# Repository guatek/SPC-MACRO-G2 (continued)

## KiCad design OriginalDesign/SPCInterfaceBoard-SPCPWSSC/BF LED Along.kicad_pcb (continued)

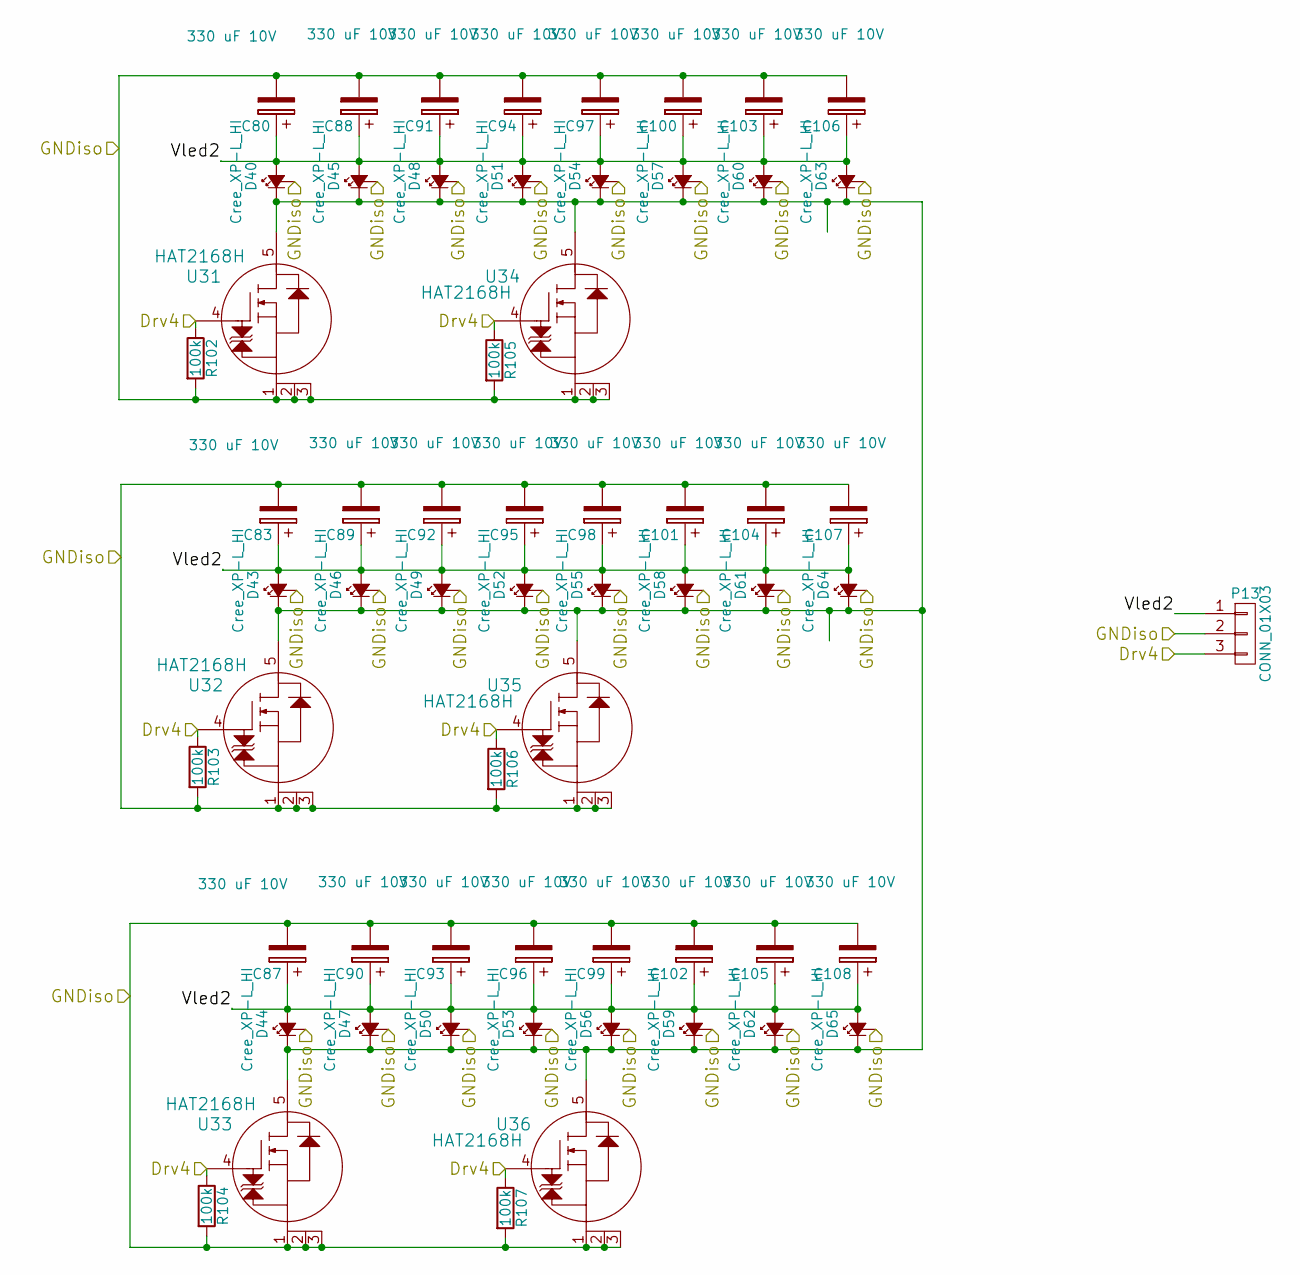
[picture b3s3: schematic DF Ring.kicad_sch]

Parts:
C80, C83, C87, C88, C89, C90, C91, C92, C93, C94, C95, C96, C97, C98, C99, C100, C101, C102, C103, C104, C105, C106, C107, C108: 330 uF 10V; TantalC_SizeD_EIA-7343_Reflow
D40, D43, D44, D45, D46, D47, D48, D49, D50, D51, D52, D53, D54, D55, D56, D57, D58, D59, D60, D61, D62, D63, D64, D65: Cree_XP-L_HI; Cree_XP-L_HI-vias-4
P13: CONN_01X03; mpt_0,5%2f3-2,54
R102, R103, R104, R105, R106, R107: 100k; r_0603
U31, U32, U33, U34, U35, U36: HAT2168H; SOT-669_LFPAK-vias

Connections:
/LED-DC-DC/Df Ring/Drv4: P13.3, R102.1, R103.1, R104.1, R105.1, R106.1, R107.1, U31.4, U32.4, U33.4, U34.4, U35.4, U36.4
/LED-DC-DC/Df Ring/GNDiso: C80.2, C83.2, C87.2, C88.2, C89.2, C90.2, C91.2, C92.2, C93.2, C94.2, C95.2, C96.2, C97.2, C98.2, C99.2, C100.2, C101.2, C102.2, C103.2, C104.2, C105.2, C106.2, C107.2, C108.2, D40.3 (PAD), D43.3 (PAD), D44.3 (PAD), D45.3 (PAD), D46.3 (PAD), D47.3 (PAD), D48.3 (PAD), D49.3 (PAD), D50.3 (PAD), D51.3 (PAD), D52.3 (PAD), D53.3 (PAD), D54.3 (PAD), D55.3 (PAD), D56.3 (PAD), D57.3 (PAD), D58.3 (PAD), D59.3 (PAD), D60.3 (PAD), D61.3 (PAD), D62.3 (PAD), D63.3 (PAD), D64.3 (PAD), D65.3 (PAD), P13.2, R102.2, R103.2, R104.2, R105.2, R106.2, R107.2, U31.1, U31.2, U31.3, U32.1, U32.2, U32.3, U33.1, U33.2, U33.3, U34.1, U34.2, U34.3, U35.1, U35.2, U35.3, U36.1, U36.2, U36.3
/LED-DC-DC/Df Ring/Vled2: C80.1, C83.1, C87.1, C88.1, C89.1, C90.1, C91.1, C92.1, C93.1, C94.1, C95.1, C96.1, C97.1, C98.1, C99.1, C100.1, C101.1, C102.1, C103.1, C104.1, C105.1, C106.1, C107.1, C108.1, D40.2 (A), D43.2 (A), D44.2 (A), D45.2 (A), D46.2 (A), D47.2 (A), D48.2 (A), D49.2 (A), D50.2 (A), D51.2 (A), D52.2 (A), D53.2 (A), D54.2 (A), D55.2 (A), D56.2 (A), D57.2 (A), D58.2 (A), D59.2 (A), D60.2 (A), D61.2 (A), D62.2 (A), D63.2 (A), D64.2 (A), D65.2 (A), P13.1
unnamed: D40.1 (K), D43.1 (K), D44.1 (K), D45.1 (K), D46.1 (K), D47.1 (K), D48.1 (K), D49.1 (K), D50.1 (K), D51.1 (K), D52.1 (K), D53.1 (K), D54.1 (K), D55.1 (K), D56.1 (K), D57.1 (K), D58.1 (K), D59.1 (K), D60.1 (K), D61.1 (K), D62.1 (K), D63.1 (K), D64.1 (K), D65.1 (K), U31.5, U32.5, U33.5, U34.5, U35.5, U36.5

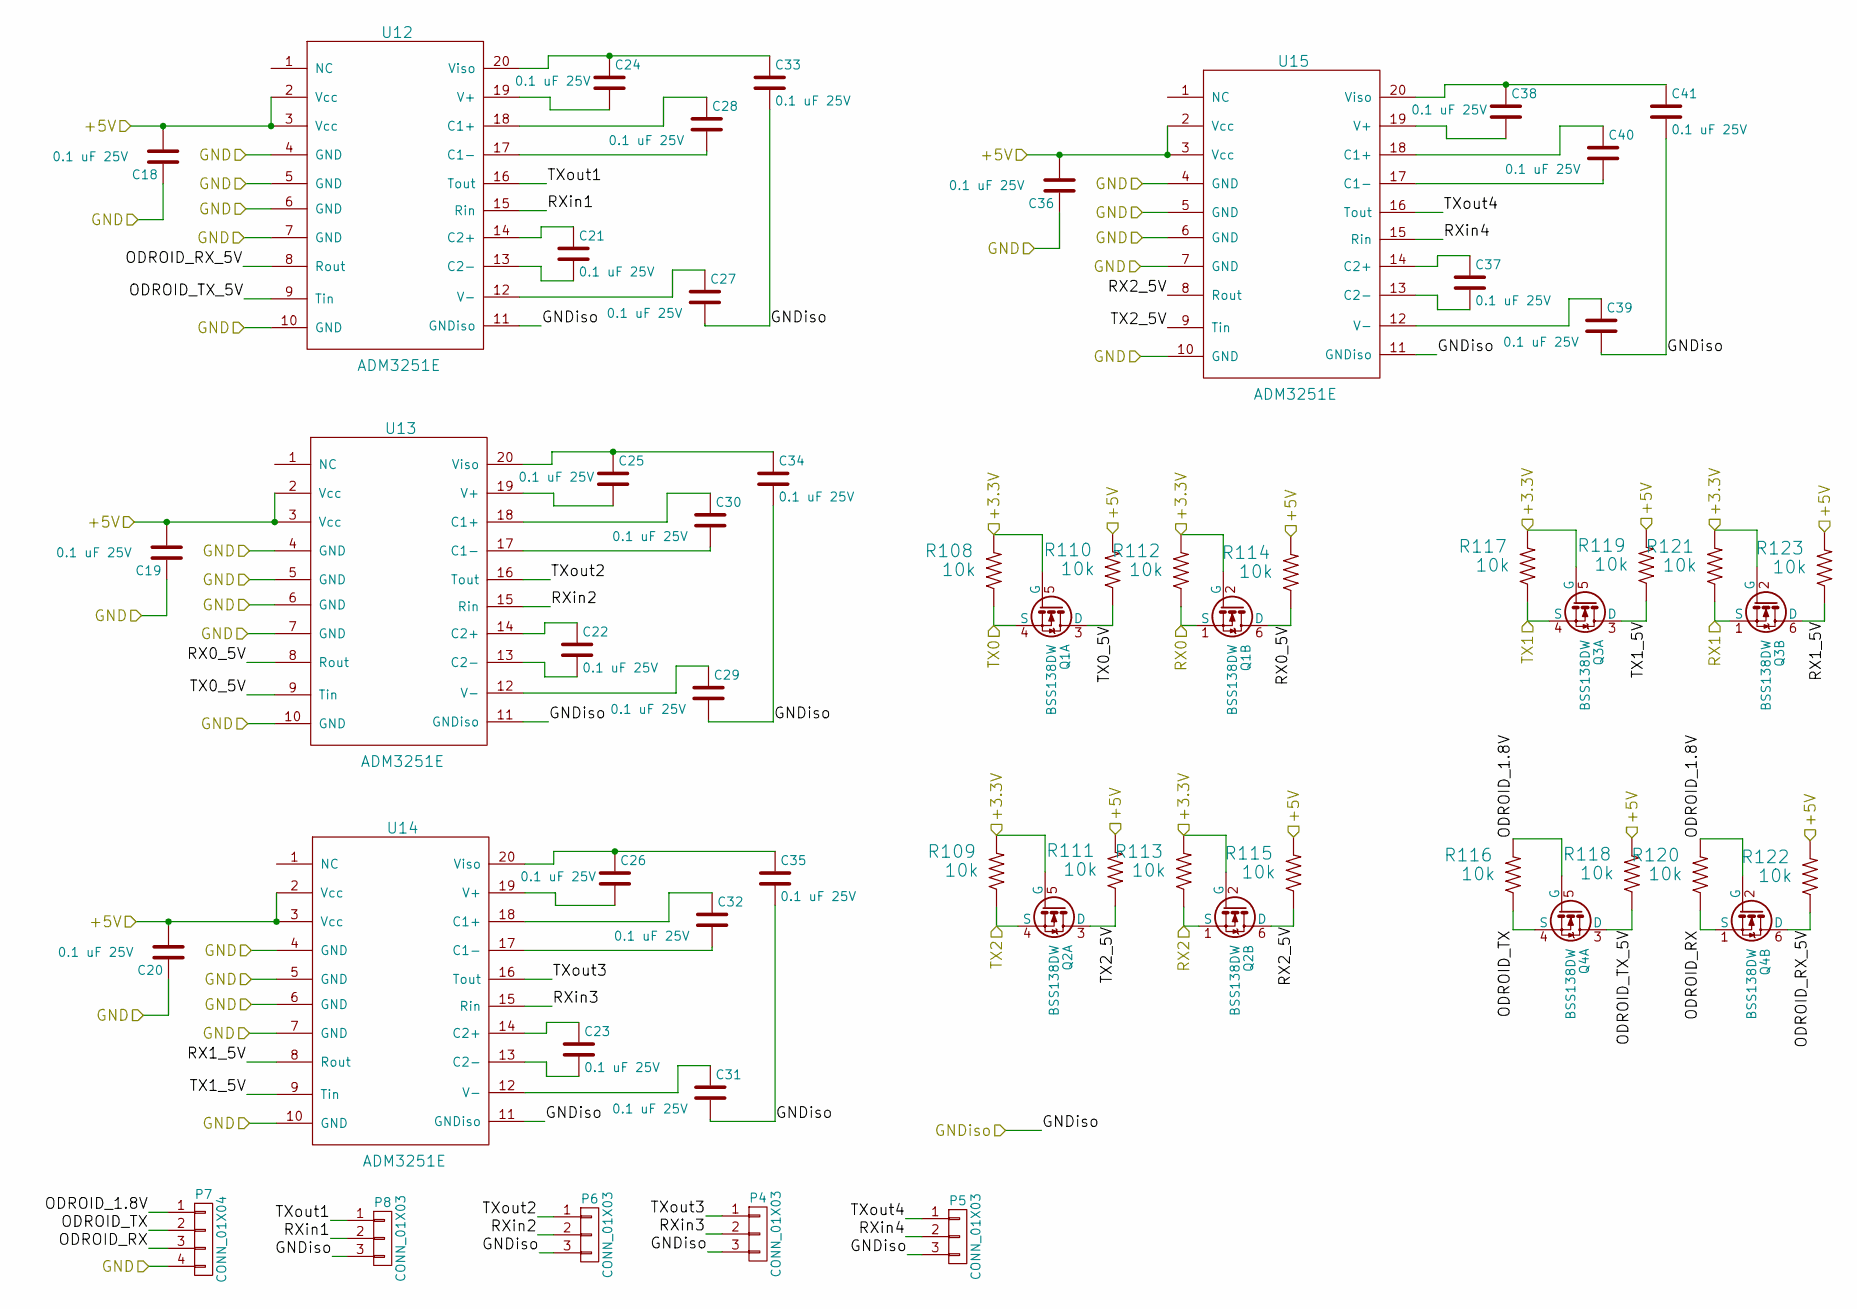
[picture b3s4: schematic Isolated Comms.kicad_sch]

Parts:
C18, C19, C20, C21, C22, C23, C24, C25, C26, C27, C28, C29, C30, C31, C32, C33, C34, C35, C36, C37, C38, C39, C40, C41: 0.1 uF 25V; c_0603
P4, P5, P6, P8: CONN_01X03; mpt_0,5%2f3-2,54
P7: CONN_01X04; mpt_0,5%2f4-2,54
Q1, Q2, Q3, Q4: BSS138DW; SOT363
R108, R109, R110, R111, R112, R113, R114, R115, R116, R117, R118, R119, R120, R121, R122, R123: 10k; r_0603
U12, U13, U14, U15: ADM3251E; SOIC-20_7.5x12.8mm_Pitch1.27mm

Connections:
/Isolated Comms/+3.3V: Q1.2 (G), Q1.5 (G), Q2.2 (G), Q2.5 (G), Q3.2 (G), Q3.5 (G), R108.2, R109.2, R112.2, R113.2, R117.2, R121.2; also elsewhere on the board
/Isolated Comms/+5V: C18.2, C19.2, C20.2, C36.2, R110.2, R111.2, R114.2, R115.2, R118.2, R119.2, R122.2, R123.2, U12.2 (Vcc), U12.3 (Vcc), U13.2 (Vcc), U13.3 (Vcc), U14.2 (Vcc), U14.3 (Vcc), U15.2 (Vcc), U15.3 (Vcc); also elsewhere on the board
/Isolated Comms/GND: C18.1, C19.1, C20.1, C36.1, P7.4, U12.4 (GND), U12.5 (GND), U12.6 (GND), U12.7 (GND), U12.10 (GND), U13.4 (GND), U13.5 (GND), U13.6 (GND), U13.7 (GND), U13.10 (GND), U14.4 (GND), U14.5 (GND), U14.6 (GND), U14.7 (GND), U14.10 (GND), U15.4 (GND), U15.5 (GND), U15.6 (GND), U15.7 (GND), U15.10 (GND); also elsewhere on the board
/Isolated Comms/GNDiso: C27.2, C29.2, C31.2, C33.2, C34.2, C35.2, C39.2, C41.2, P4.3, P5.3, P6.3, P8.3, U12.11 (GNDiso), U13.11 (GNDiso), U14.11 (GNDiso), U15.11 (GNDiso); also elsewhere on the board
/Isolated Comms/ODROID_1.8V: P7.1, Q4.2 (G), Q4.5 (G), R116.2, R120.2
/Isolated Comms/ODROID_RX: P7.3, Q4.1 (S), R120.1
/Isolated Comms/ODROID_RX_5V: Q4.6 (D), R122.1, U12.8 (Rout)
/Isolated Comms/ODROID_TX: P7.2, Q4.4 (S), R116.1
/Isolated Comms/ODROID_TX_5V: Q4.3 (D), R118.1, U12.9 (Tin)
/Isolated Comms/RX0: Q1.1 (S), R112.1; also elsewhere on the board
/Isolated Comms/RX0_5V: Q1.6 (D), R114.1, U13.8 (Rout)
/Isolated Comms/RX1: Q3.1 (S), R121.1; also elsewhere on the board
/Isolated Comms/RX1_5V: Q3.6 (D), R123.1, U14.8 (Rout)
/Isolated Comms/RX2: Q2.1 (S), R113.1; also elsewhere on the board
/Isolated Comms/RX2_5V: Q2.6 (D), R115.1, U15.8 (Rout)
/Isolated Comms/RXin1: P8.2, U12.15 (Rin)
/Isolated Comms/RXin2: P6.2, U13.15 (Rin)
/Isolated Comms/RXin3: P4.2, U14.15 (Rin)
/Isolated Comms/RXin4: P5.2, U15.15 (Rin)
/Isolated Comms/TX0: Q1.4 (S), R108.1; also elsewhere on the board
/Isolated Comms/TX0_5V: Q1.3 (D), R110.1, U13.9 (Tin)
/Isolated Comms/TX1: Q3.4 (S), R117.1; also elsewhere on the board
/Isolated Comms/TX1_5V: Q3.3 (D), R119.1, U14.9 (Tin)
/Isolated Comms/TX2: Q2.4 (S), R109.1; also elsewhere on the board
/Isolated Comms/TX2_5V: Q2.3 (D), R111.1, U15.9 (Tin)
/Isolated Comms/TXout1: P8.1, U12.16 (Tout)
/Isolated Comms/TXout2: P6.1, U13.16 (Tout)
/Isolated Comms/TXout3: P4.1, U14.16 (Tout)
/Isolated Comms/TXout4: P5.1, U15.16 (Tout)
unnamed: C21.1, U12.14 (C2+)
unnamed: C21.2, U12.13 (C2-)
unnamed: C22.1, U13.14 (C2+)
unnamed: C22.2, U13.13 (C2-)
unnamed: C23.1, U14.14 (C2+)
unnamed: C23.2, U14.13 (C2-)
unnamed: C24.1, C33.1, U12.20 (Viso)
unnamed: C24.2, U12.19 (V+)
unnamed: C25.1, C34.1, U13.20 (Viso)
unnamed: C25.2, U13.19 (V+)
unnamed: C26.1, C35.1, U14.20 (Viso)
unnamed: C26.2, U14.19 (V+)
unnamed: C27.1, U12.12 (V-)
unnamed: C28.1, U12.18 (C1+)
unnamed: C28.2, U12.17 (C1-)
unnamed: C29.1, U13.12 (V-)
unnamed: C30.1, U13.18 (C1+)
unnamed: C30.2, U13.17 (C1-)
unnamed: C31.1, U14.12 (V-)
unnamed: C32.1, U14.18 (C1+)
unnamed: C32.2, U14.17 (C1-)
unnamed: C37.1, U15.14 (C2+)
unnamed: C37.2, U15.13 (C2-)
unnamed: C38.1, C41.1, U15.20 (Viso)
unnamed: C38.2, U15.19 (V+)
unnamed: C39.1, U15.12 (V-)
unnamed: C40.1, U15.18 (C1+)
unnamed: C40.2, U15.17 (C1-)

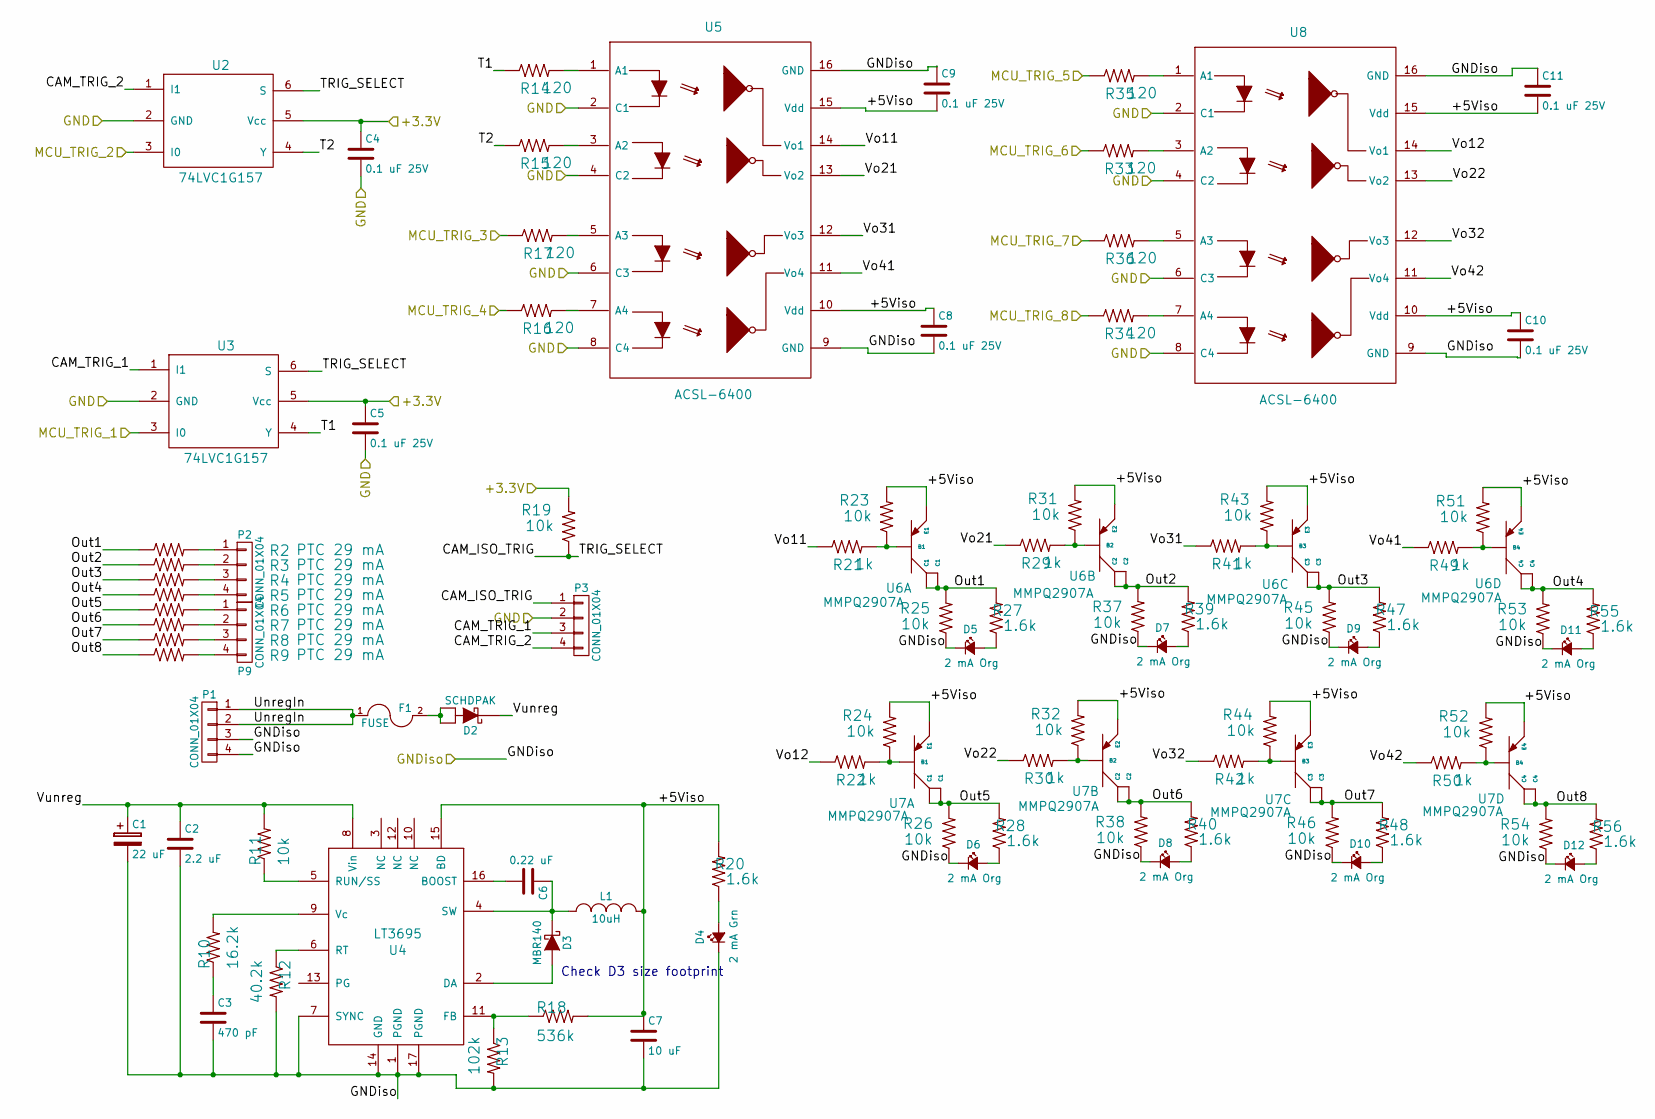
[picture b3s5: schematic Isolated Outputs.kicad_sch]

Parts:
C1: 22 uF; c_tant_X
C2: 2.2 uF; c_0805
C3: 470 pF; c_0603
C4, C5, C8, C9, C10, C11: 0.1 uF 25V; c_0603
C6: 0.22 uF; c_0603
C7: 10 uF; c_1210
D2: SCHDPAK; d-pak
D3: MBR140; SOD-123FL
D4: 2 mA Grn; LED_0805
D5, D6, D7, D8, D9, D10, D11, D12: 2 mA Org; LED_0805
F1: FUSE; Fuse_SMD
L1: 10uH; c_2220
P1, P2, P3, P9: CONN_01X04; mpt_0,5%2f4-2,54
R2, R3, R4, R5, R6, R7, R8, R9: PTC 29 mA; r_0603
R10: 16.2k; r_0603
R11, R19, R23, R24, R25, R26, R31, R32, R37, R38, R43, R44, R45, R46, R51, R52, R53, R54: 10k; r_0603
R12: 40.2k; r_0603
R13: 102k; r_0603
R14, R15, R16, R17, R33, R34, R35, R36: 120; r_0603
R18: 536k; r_0603
R20, R27, R28, R39, R40, R47, R48, R55, R56: 1.6k; r_0603
R21, R22, R29, R30, R41, R42, R49, R50: 1k; r_0603
U2, U3: 74LVC1G157; SC-74
U4: LT3695; MSOP-16-1EP-VIA_3x4mm_Pitch0.5mm
U5, U8: ACSL-6400; SOIC-16_3.9x9.9mm_Pitch1.27mm
U6, U7: MMPQ2907A; SO-16-N

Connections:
/Isolated Comms/+3.3V: C4.1, C5.1, R19.2, U2.5 (Vcc), U3.5 (Vcc); also elsewhere on the board
/Isolated Comms/GND: C4.2, C5.2, P3.2, U2.2 (GND), U3.2 (GND), U5.2 (C1), U5.4 (C2), U5.6 (C3), U5.8 (C4), U8.2 (C1), U8.4 (C2), U8.6 (C3), U8.8 (C4); also elsewhere on the board
/Isolated Comms/GNDiso: C1.2, C2.2, C3.2, C7.2, C8.2, C9.1, C10.2, C11.1, D4.1 (K), D5.1 (K), D6.1 (K), D7.1 (K), D8.1 (K), D9.1 (K), D10.1 (K), D11.1 (K), D12.1 (K), P1.3, P1.4, R12.2, R13.2, R25.1, R26.1, R37.1, R38.1, R45.1, R46.1, R53.1, R54.1, U4.1 (PGND), U4.7 (SYNC), U4.14 (GND), U4.17 (PGND), U5.9 (GND), U5.16 (GND), U8.9 (GND), U8.16 (GND); also elsewhere on the board
/Isolated Outputs/+5Viso: C7.1, C8.1, C9.2, C10.1, C11.2, L1.2, R18.2, R20.2, R23.2, R24.2, R31.2, R32.2, R43.2, R44.2, R51.2, R52.2, U4.15 (BD), U5.10 (Vdd), U5.15 (Vdd), U6.10 (E4), U6.12 (E3), U6.14 (E2), U6.16 (E1), U7.10 (E4), U7.12 (E3), U7.14 (E2), U7.16 (E1), U8.10 (Vdd), U8.15 (Vdd)
/Isolated Outputs/CAM_ISO_TRIG: P3.1, R19.1, U2.6 (S), U3.6 (S)
/Isolated Outputs/CAM_TRIG_1: P3.3, U3.1 (I1)
/Isolated Outputs/CAM_TRIG_2: P3.4, U2.1 (I1)
/Isolated Outputs/MCU_TRIG_1: U3.3 (I0); also elsewhere on the board
/Isolated Outputs/MCU_TRIG_2: U2.3 (I0); also elsewhere on the board
/Isolated Outputs/MCU_TRIG_3: R17.1; also elsewhere on the board
/Isolated Outputs/MCU_TRIG_4: R16.1; also elsewhere on the board
/Isolated Outputs/MCU_TRIG_5: R35.1; also elsewhere on the board
/Isolated Outputs/MCU_TRIG_6: R33.1; also elsewhere on the board
/Isolated Outputs/MCU_TRIG_7: R36.1; also elsewhere on the board
/Isolated Outputs/MCU_TRIG_8: R34.1; also elsewhere on the board
/Isolated Outputs/Out1: R2.1, R25.2, R27.2, U6.1 (C1), U6.2 (C1)
/Isolated Outputs/Out2: R3.1, R37.2, R39.2, U6.3 (C2), U6.4 (C2)
/Isolated Outputs/Out3: R4.1, R45.2, R47.2, U6.5 (C3), U6.6 (C3)
/Isolated Outputs/Out4: R5.1, R53.2, R55.2, U6.7 (C4), U6.8 (C4)
/Isolated Outputs/Out5: R6.1, R26.2, R28.2, U7.1 (C1), U7.2 (C1)
/Isolated Outputs/Out6: R7.1, R38.2, R40.2, U7.3 (C2), U7.4 (C2)
/Isolated Outputs/Out7: R8.1, R46.2, R48.2, U7.5 (C3), U7.6 (C3)
/Isolated Outputs/Out8: R9.1, R54.2, R56.2, U7.7 (C4), U7.8 (C4)
/Isolated Outputs/T1: R14.1, U3.4 (Y)
/Isolated Outputs/T2: R15.1, U2.4 (Y)
/Isolated Outputs/UnregIn: F1.1, P1.1, P1.2
/Isolated Outputs/Vo11: R21.1, U5.14 (Vo1)
/Isolated Outputs/Vo12: R22.1, U8.14 (Vo1)
/Isolated Outputs/Vo21: R29.1, U5.13 (Vo2)
/Isolated Outputs/Vo22: R30.1, U8.13 (Vo2)
/Isolated Outputs/Vo31: R41.1, U5.12 (Vo3)
/Isolated Outputs/Vo32: R42.1, U8.12 (Vo3)
/Isolated Outputs/Vo41: R49.1, U5.11 (Vo4)
/Isolated Outputs/Vo42: R50.1, U8.11 (Vo4)
/Isolated Outputs/Vunreg: C1.1, C2.1, D2.2 (K), R11.2, U4.8 (Vin)
unnamed: C3.1, R10.1
unnamed: C6.1, D3.1 (K), L1.1, U4.4 (SW)
unnamed: C6.2, U4.16 (BOOST)
unnamed: D2.1 (A), D2.3 (A), F1.2
unnamed: D3.2 (A), U4.2 (DA)
unnamed: D4.2 (A), R20.1
unnamed: D5.2 (A), R27.1
unnamed: D6.2 (A), R28.1
unnamed: D7.2 (A), R39.1
unnamed: D8.2 (A), R40.1
unnamed: D9.2 (A), R47.1
unnamed: D10.2 (A), R48.1
unnamed: D11.2 (A), R55.1
unnamed: D12.2 (A), R56.1
unnamed: P2.1, R2.2
unnamed: P2.2, R3.2
unnamed: P2.3, R4.2
unnamed: P2.4, R5.2
unnamed: P9.1, R6.2
unnamed: P9.2, R7.2
unnamed: P9.3, R8.2
unnamed: P9.4, R9.2
unnamed: R10.2, U4.9 (Vc)
unnamed: R11.1, U4.5 (RUN/SS)
unnamed: R12.1, U4.6 (RT)
unnamed: R13.1, R18.1, U4.11 (FB)
unnamed: R14.2, U5.1 (A1)
unnamed: R15.2, U5.3 (A2)
unnamed: R16.2, U5.7 (A4)
unnamed: R17.2, U5.5 (A3)
unnamed: R21.2, R23.1, U6.15 (B1)
unnamed: R22.2, R24.1, U7.15 (B1)
unnamed: R29.2, R31.1, U6.13 (B2)
unnamed: R30.2, R32.1, U7.13 (B2)
unnamed: R33.2, U8.3 (A2)
unnamed: R34.2, U8.7 (A4)
unnamed: R35.2, U8.1 (A1)
unnamed: R36.2, U8.5 (A3)
unnamed: R41.2, R43.1, U6.11 (B3)
unnamed: R42.2, R44.1, U7.11 (B3)
unnamed: R49.2, R51.1, U6.9 (B4)
unnamed: R50.2, R52.1, U7.9 (B4)

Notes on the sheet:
Check D3 size footprint

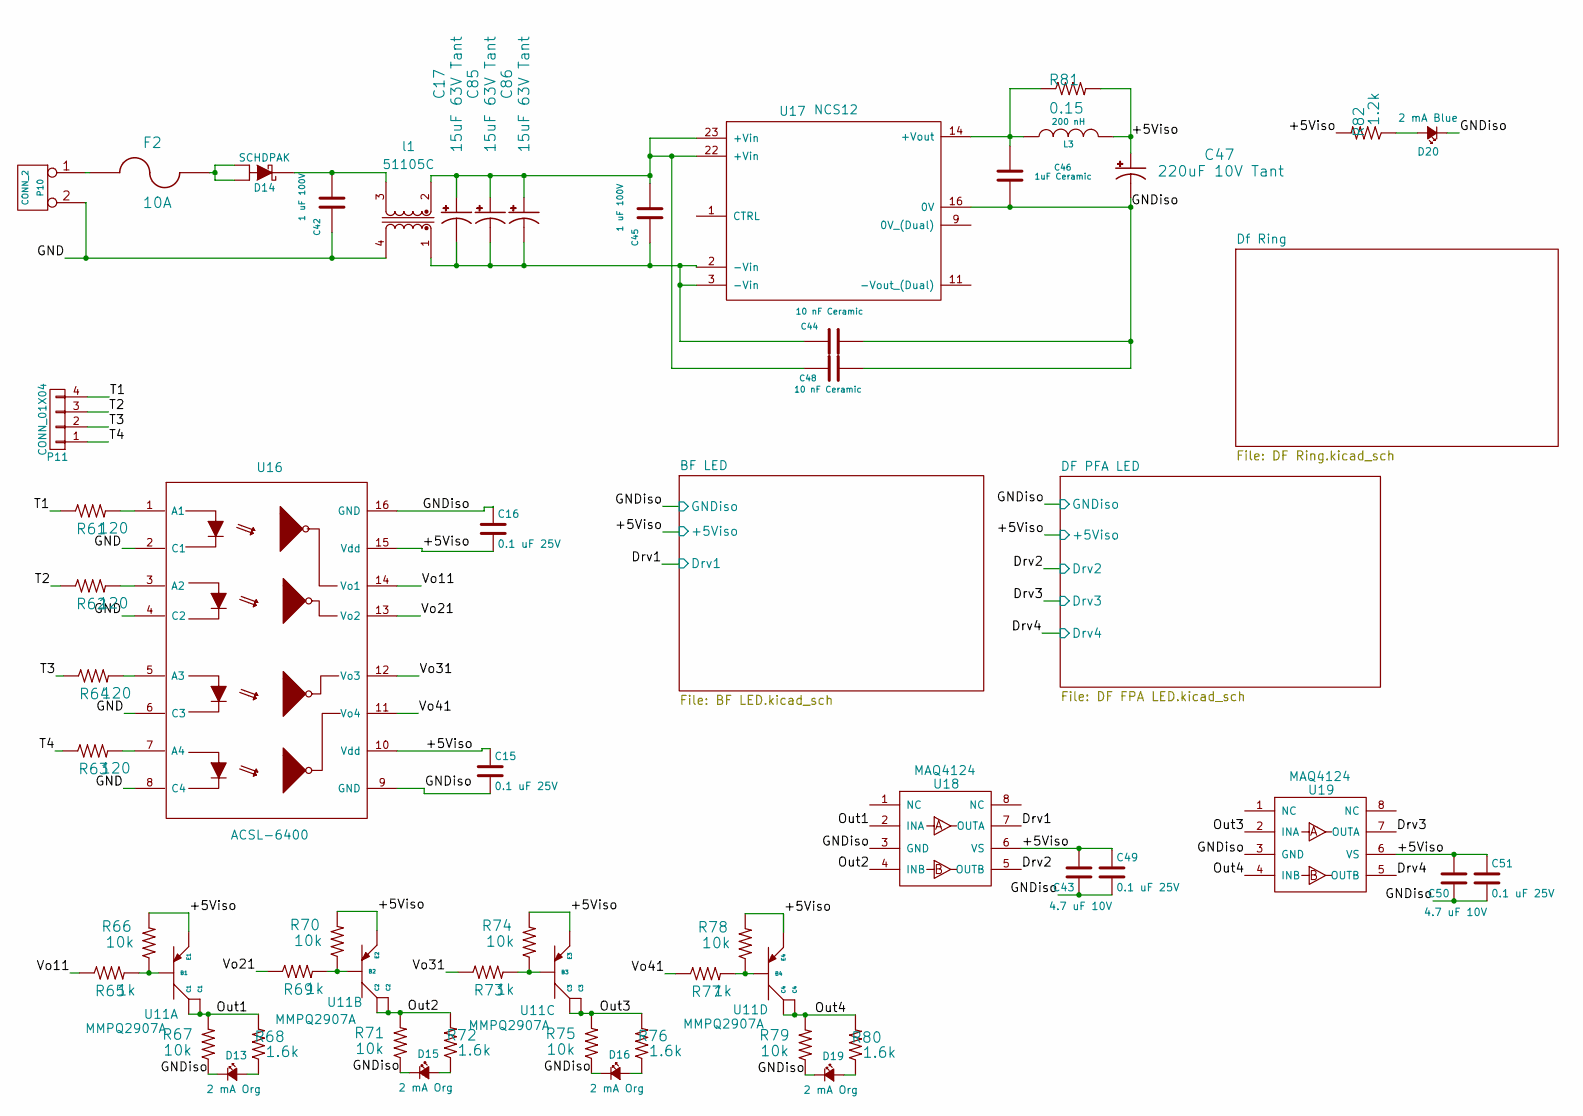
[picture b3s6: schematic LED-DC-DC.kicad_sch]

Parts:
C15, C16, C49, C51: 0.1 uF 25V; c_0603
C17, C85, C86: 15uF 63V Tant; TantalC_SizeD_EIA-7343_Reflow
C42, C45: 1 uF 100V; c_0805
C43, C50: 4.7 uF 10V; c_0603
C44, C48: 10 nF Ceramic; C_1210
C46: 1uF Ceramic; c_0805
C47: 220uF 10V Tant; TantalC_SizeD_EIA-7343_Reflow
D13, D15, D16, D19: 2 mA Org; LED_0805
D14: SCHDPAK; d-pak
D20: 2 mA Blue; LED_0805
F2: 10A; Fuse_SMD
L3: 200 nH; IHLP-1212BZ-11
P10: CONN_2; mpt_0,5%2f2-2,54
P11: CONN_01X04; mpt_0,5%2f4-2,54
R61, R62, R63, R64: 120; r_0603
R65, R69, R73, R77: 1k; r_0603
R66, R67, R70, R71, R74, R75, R78, R79: 10k; r_0603
R68, R72, R76, R80: 1.6k; r_0603
R81: 0.15; r_1206
R82: 1.2k; r_0603
U11: MMPQ2907A; SO-16-N
U16: ACSL-6400; SOIC-16_3.9x9.9mm_Pitch1.27mm
U17: NCS12
U18, U19: MAQ4124; SOIC-8-1EP_3.9x4.9mm_Pitch1.27mm
l1: 51105C

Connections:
/LED-DC-DC/BF LED/+5Viso: C15.1, C16.2, C43.2, C47.1 (+), C49.1, C50.2, C51.1, L3.2, R66.2, R70.2, R74.2, R78.2, R81.2, R82.2, U11.10 (E4), U11.12 (E3), U11.14 (E2), U11.16 (E1), U16.10 (Vdd), U16.15 (Vdd), U18.6 (VS), U19.6 (VS); also elsewhere on the board
/LED-DC-DC/BF LED/Drv1: U18.7 (OUTA); also elsewhere on the board
/LED-DC-DC/DF PFA LED/Drv2: U18.5 (OUTB); also elsewhere on the board
/LED-DC-DC/DF PFA LED/Drv3: U19.7 (OUTA); also elsewhere on the board
/LED-DC-DC/DF PFA LED/Drv4: U19.5 (OUTB); also elsewhere on the board
/LED-DC-DC/GND: C42.1, P10.2 (PM), U16.2 (C1), U16.4 (C2), U16.6 (C3), U16.8 (C4), l1.4
/LED-DC-DC/Out1: R67.2, R68.2, U11.1 (C1), U11.2 (C1), U18.2 (INA)
/LED-DC-DC/Out2: R71.2, R72.2, U11.3 (C2), U11.4 (C2), U18.4 (INB)
/LED-DC-DC/Out3: R75.2, R76.2, U11.5 (C3), U11.6 (C3), U19.2 (INA)
/LED-DC-DC/Out4: R79.2, R80.2, U11.7 (C4), U11.8 (C4), U19.4 (INB)
/LED-DC-DC/T1: P11.4, R61.1
/LED-DC-DC/T2: P11.3, R62.1
/LED-DC-DC/T3: P11.2, R64.1
/LED-DC-DC/T4: P11.1, R63.1
/LED-DC-DC/Vo11: R65.1, U16.14 (Vo1)
/LED-DC-DC/Vo21: R69.1, U16.13 (Vo2)
/LED-DC-DC/Vo31: R73.1, U16.12 (Vo3)
/LED-DC-DC/Vo41: R77.1, U16.11 (Vo4)
unnamed: C17.1 (+), C45.2, C48.1, C85.1 (+), C86.1 (+), U17.22 (+Vin), U17.23 (+Vin), l1.2
unnamed: C17.2, C44.1, C45.1, C85.2, C86.2, U17.2 (-Vin), U17.3 (-Vin), l1.1
unnamed: C42.2, D14.2 (K), l1.3
unnamed: C46.1, L3.1, R81.1, U17.14 (+Vout)
unnamed: D13.2 (A), R68.1
unnamed: D14.1 (A), D14.3 (A), F2.2
unnamed: D15.2 (A), R72.1
unnamed: D16.2 (A), R76.1
unnamed: D19.2 (A), R80.1
unnamed: D20.2 (A), R82.1
unnamed: F2.1, P10.1
unnamed: R61.2, U16.1 (A1)
unnamed: R62.2, U16.3 (A2)
unnamed: R63.2, U16.7 (A4)
unnamed: R64.2, U16.5 (A3)
unnamed: R65.2, R66.1, U11.15 (B1)
unnamed: R69.2, R70.1, U11.13 (B2)
unnamed: R73.2, R74.1, U11.11 (B3)
unnamed: R77.2, R78.1, U11.9 (B4)

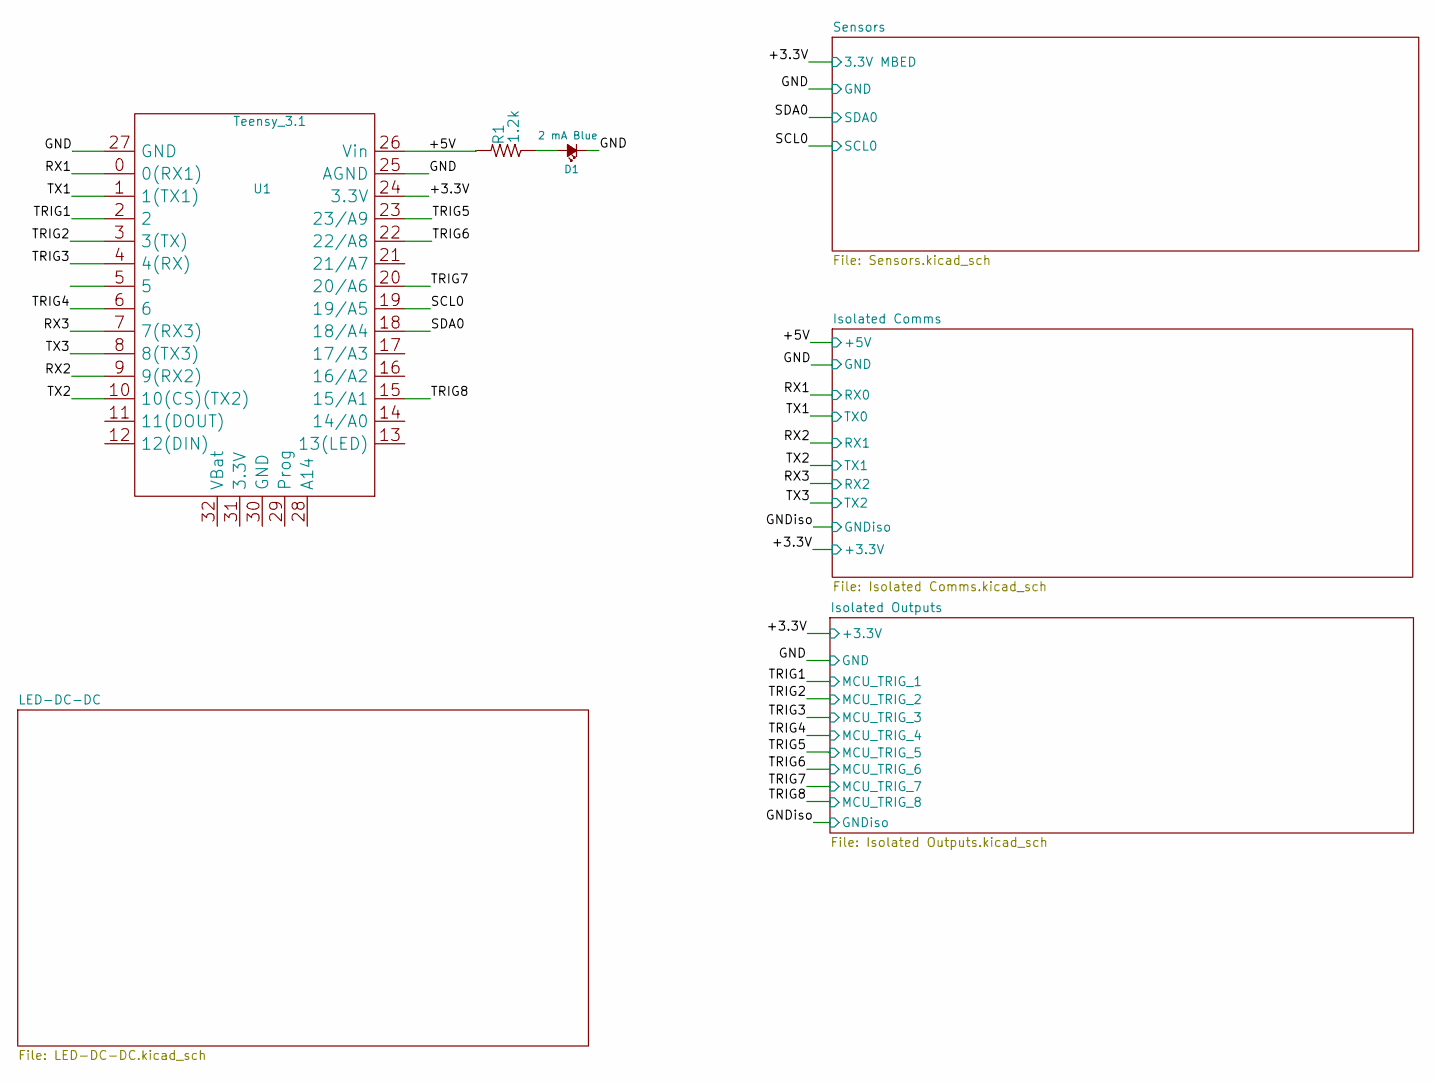
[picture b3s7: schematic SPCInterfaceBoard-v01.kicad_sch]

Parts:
D1: 2 mA Blue; LED_0805
R1: 1.2k; r_0603
U1: Teensy_3.1; Teensy-3.1

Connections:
/Isolated Comms/+3.3V: U1.24 (3.3V); also elsewhere on the board
/Isolated Comms/+5V: R1.2, U1.26 (Vin); also elsewhere on the board
/Isolated Comms/GND: D1.1 (K), U1.25 (AGND), U1.27 (GND); also elsewhere on the board
/Isolated Comms/RX0: U1.0 (0(RX1)); also elsewhere on the board
/Isolated Comms/RX1: U1.9 (9(RX2)); also elsewhere on the board
/Isolated Comms/RX2: U1.7 (7(RX3)); also elsewhere on the board
/Isolated Comms/TX0: U1.1 (1(TX1)); also elsewhere on the board
/Isolated Comms/TX1: U1.10 (10(CS)(TX2)); also elsewhere on the board
/Isolated Comms/TX2: U1.8 (8(TX3)); also elsewhere on the board
/Isolated Outputs/MCU_TRIG_1: U1.2; also elsewhere on the board
/Isolated Outputs/MCU_TRIG_2: U1.3 (3(TX)); also elsewhere on the board
/Isolated Outputs/MCU_TRIG_3: U1.4 (4(RX)); also elsewhere on the board
/Isolated Outputs/MCU_TRIG_4: U1.6; also elsewhere on the board
/Isolated Outputs/MCU_TRIG_5: U1.23 (23/A9); also elsewhere on the board
/Isolated Outputs/MCU_TRIG_6: U1.22 (22/A8); also elsewhere on the board
/Isolated Outputs/MCU_TRIG_7: U1.20 (20/A6); also elsewhere on the board
/Isolated Outputs/MCU_TRIG_8: U1.15 (15/A1); also elsewhere on the board
/Sensors/SCL0: U1.19 (19/A5); also elsewhere on the board
/Sensors/SDA0: U1.18 (18/A4); also elsewhere on the board
unnamed: D1.2 (A), R1.1

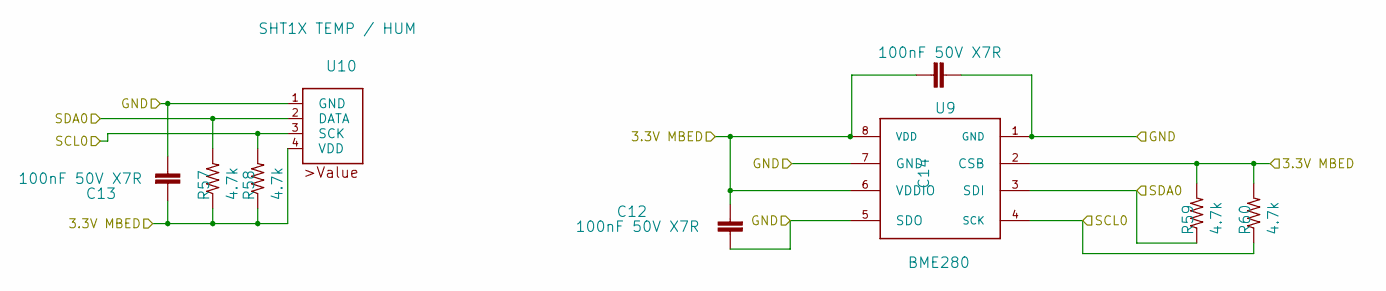
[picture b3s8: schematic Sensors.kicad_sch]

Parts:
C12, C13, C14: 100nF 50V X7R; c_0805
R57, R58, R59, R60: 4.7k; r_0603
U9: BME280
U10: SHT1X TEMP / HUM; SHT1X

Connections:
/Isolated Comms/+3.3V: C12.2, C13.2, C14.2, R57.1, R58.1, R59.2, R60.2, U9.2 (CSB), U9.6 (VDDIO), U9.8 (VDD), U10.4 (VDD); also elsewhere on the board
/Isolated Comms/GND: C12.1, C13.1, C14.1, U9.1 (GND), U9.5 (SDO), U9.7 (GND), U10.1 (GND); also elsewhere on the board
/Sensors/SCL0: R58.2, R60.1, U9.4 (SCK), U10.3 (SCK); also elsewhere on the board
/Sensors/SDA0: R57.2, R59.1, U9.3 (SDI), U10.2 (DATA); also elsewhere on the board

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
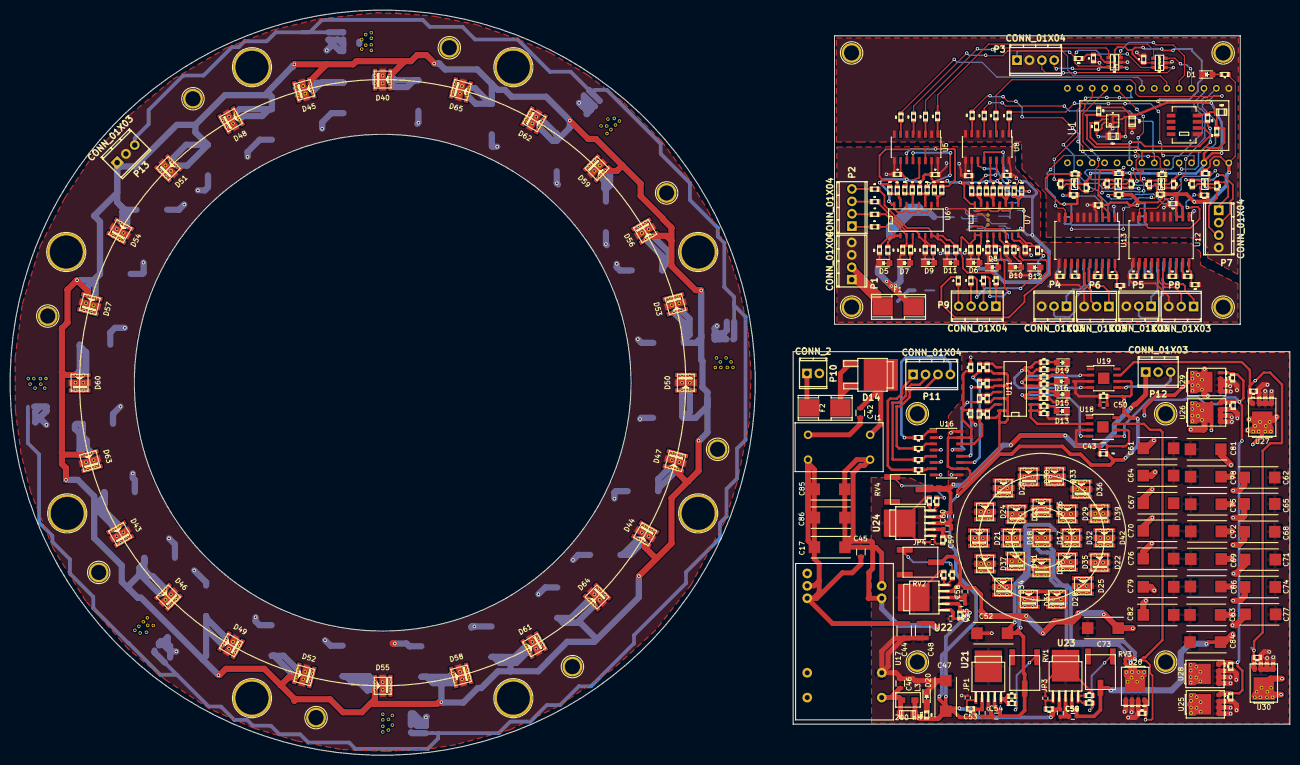
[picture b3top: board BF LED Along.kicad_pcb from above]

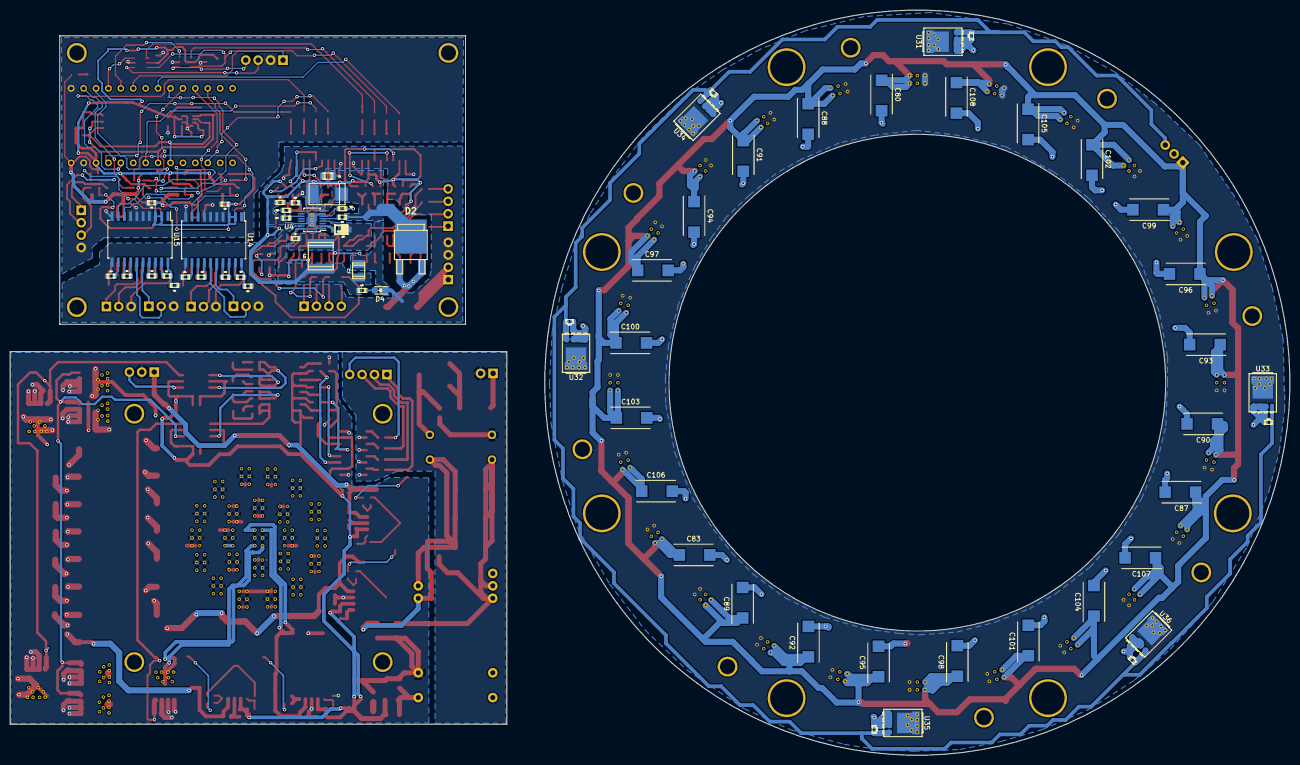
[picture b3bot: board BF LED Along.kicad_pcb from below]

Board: 4 copper layers, 261.8 x 152.4 mm, 362 parts (66 on the bottom side), 195 nets.

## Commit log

2024-04-27 Initial Import with Original Design Files
2024-08-10 Revision A, sent to PCBWay 8/10/2024 Reviwed: Layout Schematic 3D model
2024-11-12 Added UVC Project, As-Built version of SystemController.
